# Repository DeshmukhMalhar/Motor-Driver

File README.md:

Motor Driver

This Board receives a pulse like input, similat to a Servo.
The input range is from 0 degrees to 90 degrees for one direction
and 90 to 180 degrees for other direction 
The Board is still under devlopement.
It will be optimised for single sided PCB as to simplify etching and testing at home

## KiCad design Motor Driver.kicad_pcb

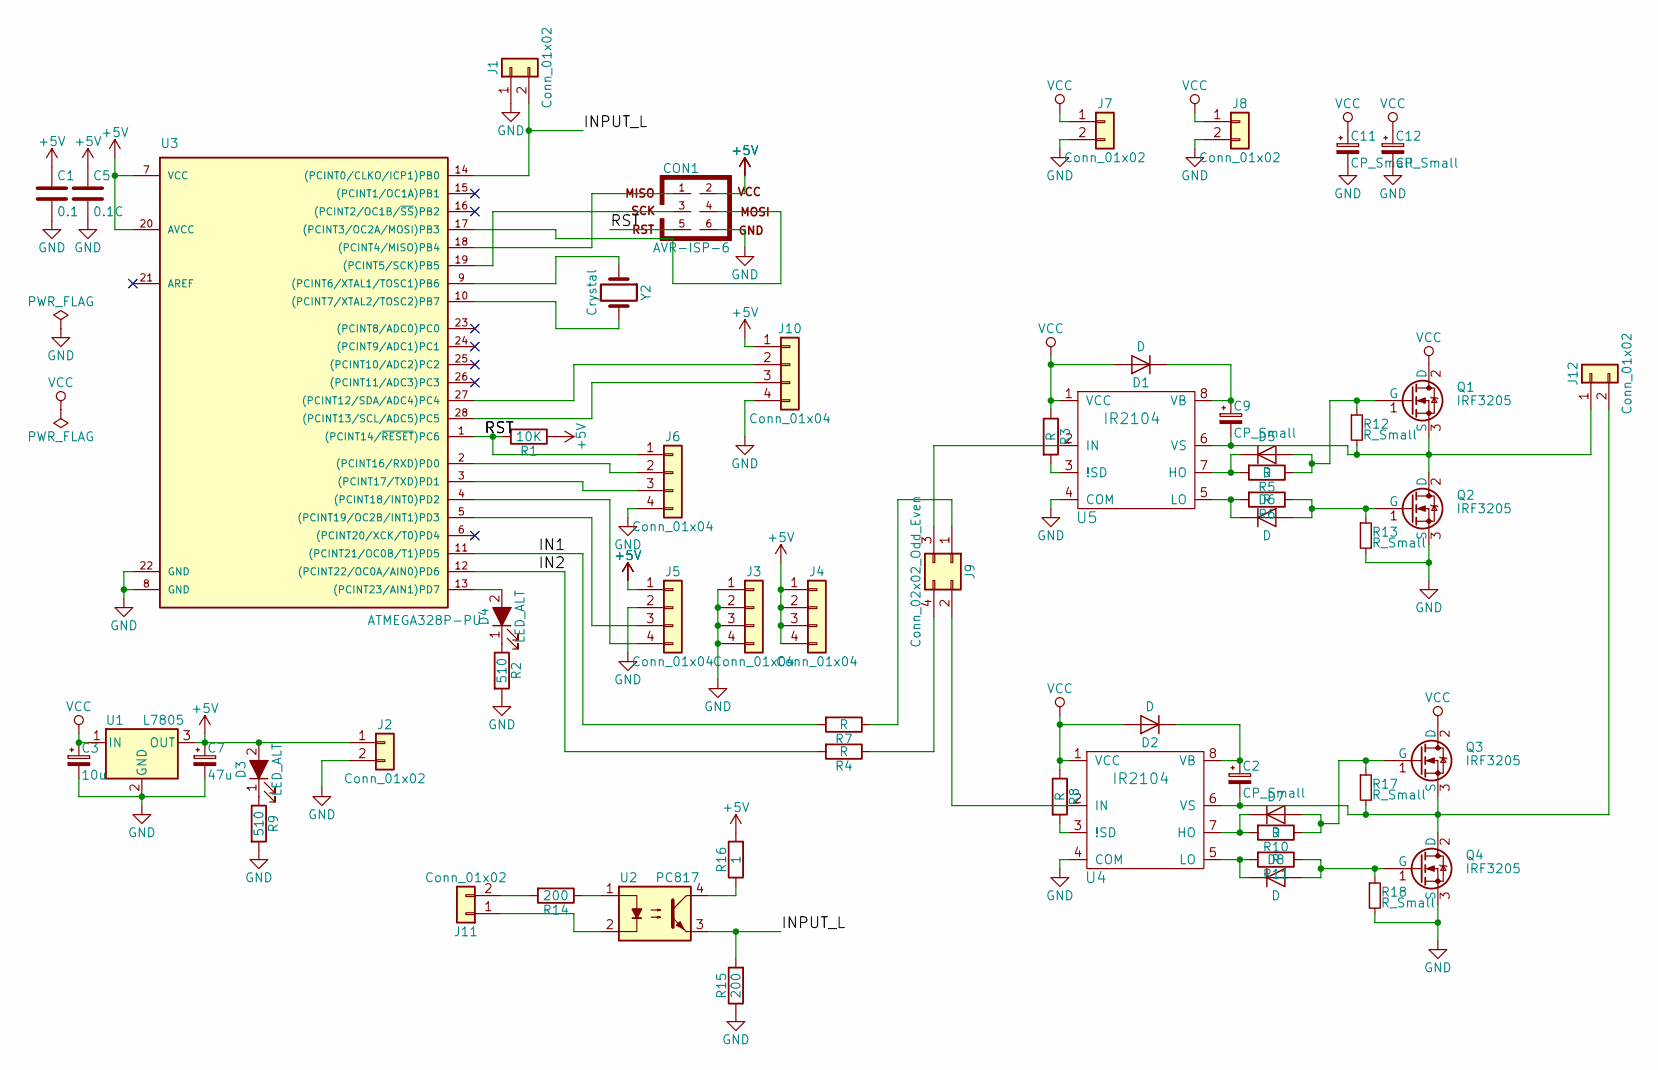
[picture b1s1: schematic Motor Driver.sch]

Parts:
C1: 0.1; C_Disc_D3.0mm_W2.0mm_P2.50mm
C2, C9: CP_Small; CP_Radial_D5.0mm_P2.00mm
C3: 10u; CP_Radial_D10.0mm_P2.50mm_P5.00mm
C5: 0.1C; C_Disc_D3.0mm_W2.0mm_P2.50mm
C7: 47u; CP_Radial_D6.3mm_P2.50mm
C11, C12: CP_Small; CP_Radial_D10.0mm_P2.50mm_P5.00mm
CON1: AVR-ISP-6; Pin_Header_Straight_2x03_Pitch2.54mm
D1, D2, D5, D6, D7, D8: D; D_A-405_P7.62mm_Horizontal
D3, D4: LED_ALT; LED_D5.0mm
J1, J2, J11: Conn_01x02; Pin_Header_Straight_1x02_Pitch2.54mm
J3, J4, J6, J10: Conn_01x04; Pin_Header_Straight_1x04_Pitch2.54mm
J5: Conn_01x04; JST_XH_B04B-XH-A_04x2.50mm_Straight
J7, J8, J12: Conn_01x02; WAGO_734_2pin_Straight_RuggedPads
J9: Conn_02x02_Odd_Even; Pin_Header_Straight_2x02_Pitch2.54mm
Q1, Q2, Q3, Q4: IRF3205; TO-220-3_Vertical
R1: 10K; R_Axial_DIN0207_L6.3mm_D2.5mm_P7.62mm_Horizontal
R2, R9: 510; R_Axial_DIN0207_L6.3mm_D2.5mm_P7.62mm_Horizontal
R3, R4, R5, R6, R7, R8, R10, R11: R; R_Axial_DIN0207_L6.3mm_D2.5mm_P7.62mm_Horizontal
R12, R13, R17, R18: R_Small; R_Axial_DIN0207_L6.3mm_D2.5mm_P7.62mm_Horizontal
R14, R15: 200; R_Axial_DIN0207_L6.3mm_D2.5mm_P7.62mm_Horizontal
R16: 1; R_Axial_DIN0207_L6.3mm_D2.5mm_P7.62mm_Horizontal
U1: L7805; TO-220-3_Vertical
U2: PC817; DIP-4_W7.62mm
U3: ATMEGA328P-PU; DIP-28_W7.62mm_Socket_LongPads
U4, U5: IR2104; DIP-8_W7.62mm_Socket_LongPads
Y2: Crystal; Crystal_HC18-U_Vertical

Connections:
+5V: C1.1, C5.1, C7.1, CON1.2, D3.2 (A), J2.1, J4.1, J4.2, J4.3, J4.4, J5.1, J10.1, R1.1, R16.2, U1.3 (OUT), U3.7 (VCC), U3.20 (AVCC)
/IN1: R7.2, U3.11 ((PCINT21/OC0B/T1)PD5)
/IN2: R4.2, U3.12 ((PCINT22/OC0A/AIN0)PD6)
/INPUT_L: J1.2, R15.2, U2.3, U3.14 ((PCINT0/CLKO/ICP1)PB0)
/RST: CON1.5, J6.1, R1.2, U3.1 ((PCINT14/~RESET~)PC6)
GND: C1.2, C3.2, C5.2, C7.2, C11.2, C12.2, CON1.6, J1.1, J2.2, J3.1, J3.2, J3.3, J3.4, J5.2, J6.4, J7.2, J8.2, J10.4, Q2.3 (S), Q4.3 (S), R2.2, R9.2, R13.2, R15.1, R18.2, U1.2 (GND), U3.8 (GND), U3.22 (GND), U4.4 (COM), U5.4 (COM)
unnamed: C2.1, D2.1 (K), U4.8 (VB)
unnamed: C2.2, J12.2, Q3.3 (S), Q4.2 (D), R17.2, U4.6 (VS)
unnamed: C9.1, D1.1 (K), U5.8 (VB)
unnamed: C9.2, J12.1, Q1.3 (S), Q2.2 (D), R12.2, U5.6 (VS)
unnamed: CON1.1, U3.18 ((PCINT4/MISO)PB4)
unnamed: CON1.3, U3.19 ((PCINT5/SCK)PB5)
unnamed: CON1.4, U3.17 ((PCINT3/OC2A/MOSI)PB3)
unnamed: D3.1 (K), R9.1
unnamed: D4.1 (K), R2.1
unnamed: D4.2 (A), U3.13 ((PCINT23/AIN1)PD7)
unnamed: D5.1 (K), R5.2, U5.7 (HO)
unnamed: D5.2 (A), Q1.1 (G), R5.1, R12.1
unnamed: D6.1 (K), R6.2, U5.5 (LO)
unnamed: D6.2 (A), Q2.1 (G), R6.1, R13.1
unnamed: D7.1 (K), R10.2, U4.7 (HO)
unnamed: D7.2 (A), Q3.1 (G), R10.1, R17.1
unnamed: D8.1 (K), R11.2, U4.5 (LO)
unnamed: D8.2 (A), Q4.1 (G), R11.1, R18.1
unnamed: J5.3, U3.5 ((PCINT19/OC2B/INT1)PD3)
unnamed: J5.4, U3.4 ((PCINT18/INT0)PD2)
unnamed: J6.2, U3.2 ((PCINT16/RXD)PD0)
unnamed: J6.3, U3.3 ((PCINT17/TXD)PD1)
unnamed: J9.1, R7.1
unnamed: J9.2, U4.2 (IN)
unnamed: J9.3, U5.2 (IN)
unnamed: J9.4, R4.1
unnamed: J10.2, U3.27 ((PCINT12/SDA/ADC4)PC4)
unnamed: J10.3, U3.28 ((PCINT13/SCL/ADC5)PC5)
unnamed: J11.1, U2.2
unnamed: J11.2, R14.2
unnamed: R3.2, U5.3 (!SD)
unnamed: R8.2, U4.3 (!SD)
unnamed: R14.1, U2.1
unnamed: R16.1, U2.4
unnamed: U3.9 ((PCINT6/XTAL1/TOSC1)PB6), Y2.1
unnamed: U3.10 ((PCINT7/XTAL2/TOSC2)PB7), Y2.2
VCC: C3.1, C11.1, C12.1, D1.2 (A), D2.2 (A), J7.1, J8.1, Q1.2 (D), Q3.2 (D), R3.1, R8.1, U1.1 (IN), U4.1 (VCC), U5.1 (VCC)

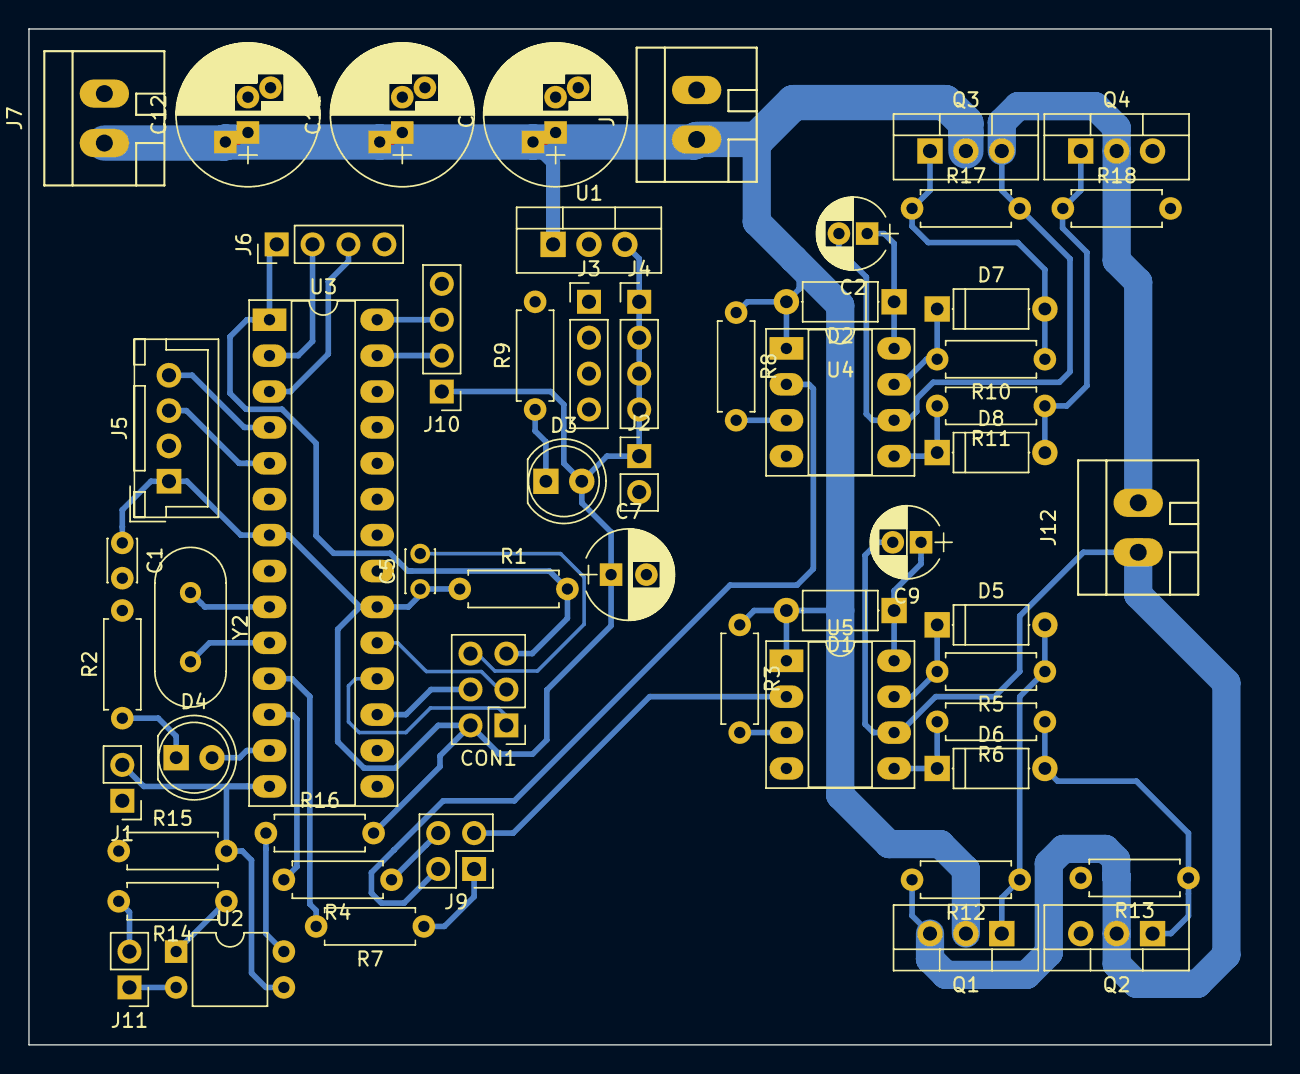
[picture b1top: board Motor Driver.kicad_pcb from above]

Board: 2 copper layers, 87.9 x 71.9 mm, 57 parts (0 on the bottom side), 43 nets.

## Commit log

2017-12-05 Added Code
2017-12-05 Update README
    Started updating Readme for upcomeing
    additions
2017-12-05 Added simulation Data
2017-12-05 Neatened up files
2017-12-09 Update dthe sketch
2017-12-09 Minor Changes
2017-12-09 Updated SCH|PCB
    Updated the SCh for polarity change on the fly using the 2x2 pinheader
    PCB was completely newly designed
2017-12-09 Nightely Update
2017-12-10 Added Isolation
    Added an Optoisolator to isolate the input signal
2017-12-11 updated 3D models
2017-12-19 Created .svg output files
2017-12-19 Seecond iteration
    Modified according to the new motor acquired
    Fixed errors in the SCH->Added gate diodes
